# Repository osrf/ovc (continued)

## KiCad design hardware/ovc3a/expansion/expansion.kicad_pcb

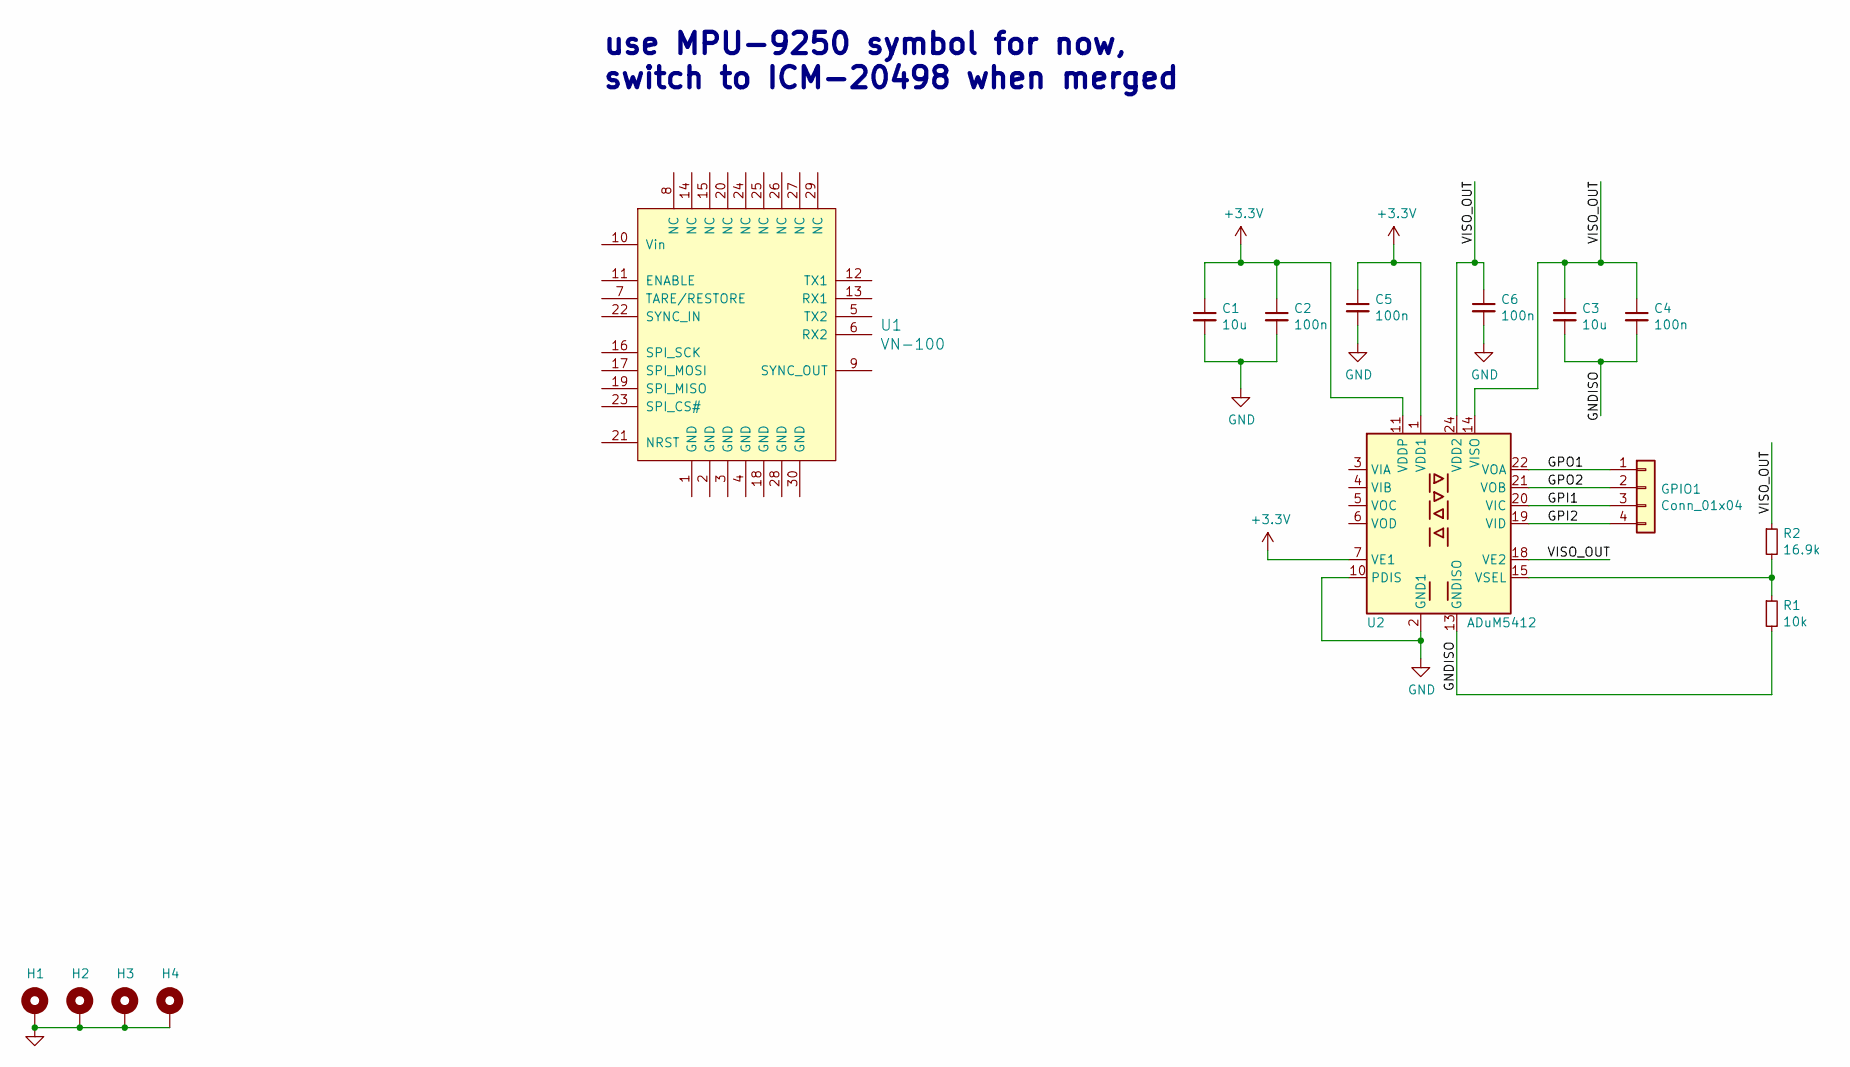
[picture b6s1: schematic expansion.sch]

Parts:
C1, C3: 10u; C_0603_1608Metric
C2, C4, C5, C6: 100n; C_0402_1005Metric
GPIO1: Conn_01x04; PinHeader_1x04_P2.54mm_Vertical
H1, H2, H3, H4: MountingHole_Pad; MountingHole_3.2mm_M3_DIN965_Pad
R1: 10k; R_0402_1005Metric
R2: 16.9k; R_0402_1005Metric
U1: VN-100
U2: ADuM5412; SSOP-24_5.3x8.2mm_P0.65mm

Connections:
+3V3: C1.1, C2.1, C5.1, U2.1 (VDD1), U2.7 (VE1), U2.11 (VDDP)
/GNDISO: C3.2, C4.2, R1.2, U2.13 (GNDISO), U2.16 (GNDISO), U2.23 (GNDISO)
/GPI1: GPIO1.3, U2.20 (VIC)
/GPI2: GPIO1.4, U2.19 (VID)
/GPO1: GPIO1.1, U2.22 (VOA)
/GPO2: GPIO1.2, U2.21 (VOB)
/VISO_OUT: C3.1, C4.1, C6.1, R2.1, U2.14 (VISO), U2.18 (VE2), U2.24 (VDD2)
GND: C1.2, C2.2, C5.2, C6.2, H1.1, H2.1, H3.1, H4.1, U2.2 (GND1), U2.9 (GND1), U2.10 (PDIS), U2.12 (GND1)
unnamed: R1.1, R2.2, U2.15 (VSEL)

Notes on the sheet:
use MPU-9250 symbol for now, switch to ICM-20498 when merged

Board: 2 copper layers, 15 parts (0 on the bottom side), 9 nets, no tracks yet.
